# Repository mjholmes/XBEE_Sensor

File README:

A simple distributed sensor board to measure temperature using a TMP36 with connectors to allow additional sensors to be fitted. All
the sensing is done using the XBEE onboard ADC.
With the correct XBEE settings it will run for over 18months off 2 AA alkaline batteries sampling one or two sensors and battery
voltage once every couple of minutes.

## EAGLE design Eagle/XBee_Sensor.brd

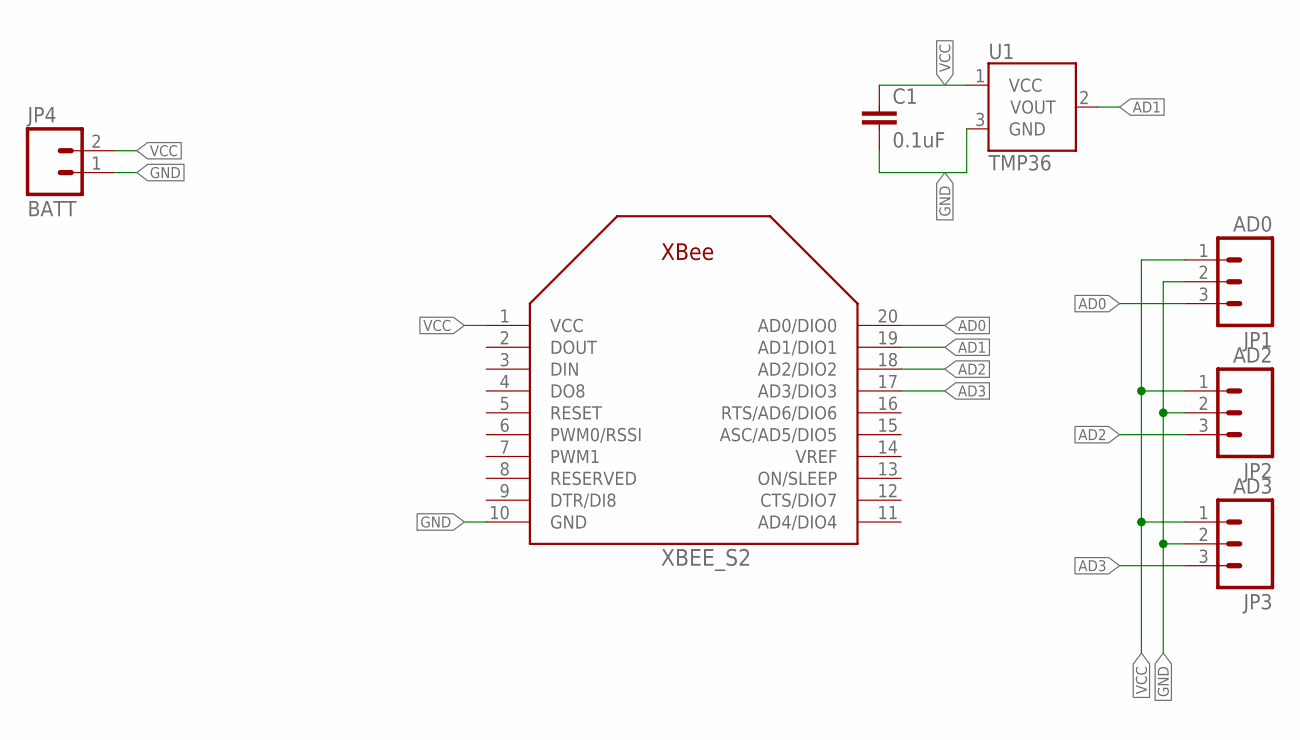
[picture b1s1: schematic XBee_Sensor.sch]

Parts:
C1: 0.1uF; C050-035X075
JP1: AD0; JST-3-PTH
JP2: AD2; JST-3-PTH
JP3: AD3; JST-3-PTH
JP4: BATT; JST-2-PTH
U1: TMP36; TO-92-AMMO
XBEE_S2: XBEE

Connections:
AD0: JP1.3, XBEE_S2.20 (AD0/DIO0)
AD1: U1.2 (VOUT), XBEE_S2.19 (AD1/DIO1)
AD2: JP2.3, XBEE_S2.18 (AD2/DIO2)
AD3: JP3.3, XBEE_S2.17 (AD3/DIO3)
GND: C1.2, JP1.2, JP2.2, JP3.2, JP4.1, U1.3 (GND), XBEE_S2.10 (GND)
VCC: C1.1, JP1.1, JP2.1, JP3.1, JP4.2, U1.1 (VCC), XBEE_S2.1 (VCC)

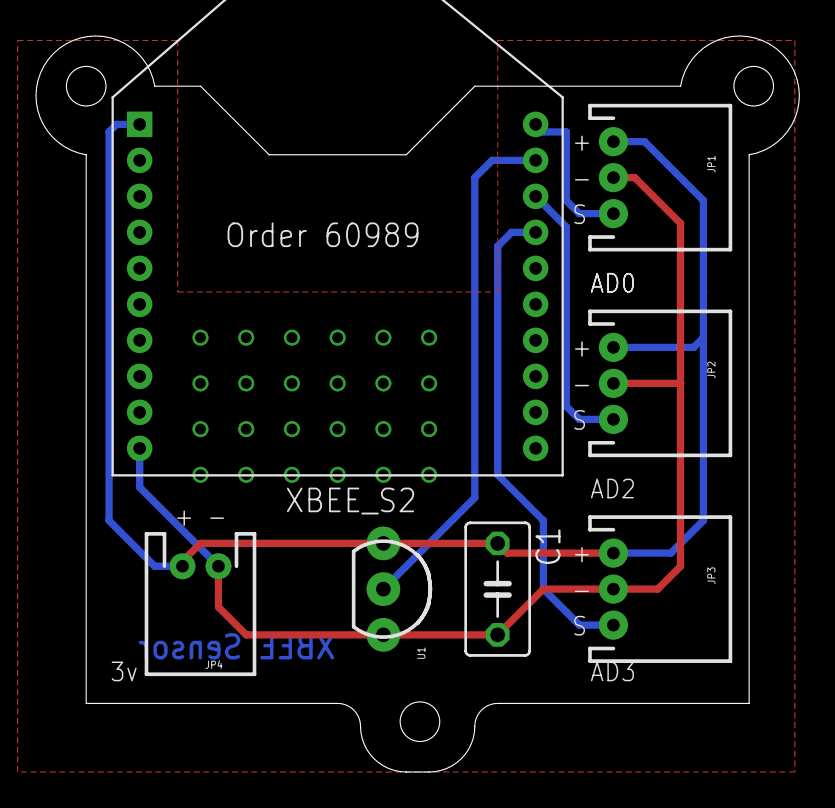
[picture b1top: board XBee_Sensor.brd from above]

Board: 2 copper layers, 42.4 x 40.9 mm, 7 parts (0 on the bottom side), 6 nets.

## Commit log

2012-10-07 Added XBEE CTU config profile
2012-10-08 Added Seeedstudio PCB order number
2013-01-05 Added coordinator X-CTU profile
2013-01-05 Fixed typo in README

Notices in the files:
parts and their libraries:
SparkFun: Licensing: CC v3.0 Share-Alike You are welcome to use this library for commercial purposes.
